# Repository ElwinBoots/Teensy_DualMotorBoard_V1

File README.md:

This project aims to deliver high performance (fast loops > 40 kHz, fast motion, and small following errors) brushless motor control.

## Videos in action 
See: https://www.youtube.com/@elwinboots2614

## Hardware 
- 1 Simple custom PCB for making connections
- 1 Teensy 4.1
- 2 DRV8301 motor drive boards, see Aliexpress
- 2 BLDC motors (sensorless or ABI encoders)
- 4 Pololu ACS711EX current sensor boards (drive boards have low side sensors. Prefer to use these instead to have in line sensing)

## Firmware
See firmware folder. Almost all code can be found in Firmware.ino. 

### Software to build firmware
"Old" Arduino IDE
- Arduino IDE 1.8.19 https://www.arduino.cc/en/software (Legacy IDE)
- Teensyduino https://www.pjrc.com/teensy/td_download.html (Follow the "Arduino 1.8.x Software Development" steps)
Or,
"New" Arduino IDE:
- Arduino IDE https://www.arduino.cc/en/software (current version: 2.2.1)
- Teensyduino https://www.pjrc.com/teensy/td_download.html (Follow the "Arduino 2.0.x Software Development" steps
 
If you want to test with 1 or 0 DRV8301 boards connected, search for the line: SPI_init( SSPIN ); and/or SPI_init( SSPIN2 ); and comment them out. With these lines commented the firmware and software can run without boards. With these lines the board waits for the DRV8301 boards, before continuing to boot.

Almost all parameters are defined in defines.h. All of these are accessible (read and write) from the host pc using the software provided. 

To add a variable and make it accessible from the PC:
1. Add parameter in defines.h 
2. run "gentracefile (Run this to update trace.h).bat". 
3. Compile and download Firmware.ino in Arduino IDE

Note: I use the 816 Mhz (overclock) option in the CPU speed menu.

## Software
- Python 3.x
- Spyder
- Code in Software folder

### To install: 
1. Download latest version of Python: https://www.python.org/downloads/
2. Install Python
3. In a command window, run `pip install spyder`
4. Run Spyder (C:\Users\XXX\AppData\Local\Programs\Python\PythonXXX\Scripts\spyder.exe)

### To use: 
1. In Spyder, run first cell (ctrl + enter) in test_object.py (for any missing modules, run `pip install <modulename>` in a cmd window.
2. When a Teensy is found with the correct firmware, you should get: "Connected to Teensy on COMX with serial number: XXXXXXXX."
3. Check that the LED on the Teensy is off. If it is still on, make check connection and power to DRV8301 boards, or comment out SPI_init( SSPIN ); and/or SPI_init( SSPIN2 ) to test without DRV8301 boards.
4. Now you can type `motor` in the IPython console, and it should show all parameters:\

5. To see for example only the configuration of motor 1, you can type `motor.conf1`:\

6. To retreive a single variable, just type the variable name and click enter. Example: `motor.state1.encoderPos1`. Note that you can use `tab` to autocomplete the name of a variable.
7. To set a variable, simply write a value to it. Example: `motor.conf1.commutationoffset = 0`, or use `m.setpar('motor.conf1.commutationoffset',0)`\
\
The setting of variables is fast. Almost 20000 values can be written in 1 second when writing one by one (even more when using arrays):\

### Tracing
To trace variables/signals: 
1. Use m.setTrace() to select signals. Example: `m.setTrace([ 'motor.state1.emech' , 'motor.state1.rmech' , 'motor.state1.ymech' ])`
2. Use `df = m.trace(2)` to trace for 2 seconds.
3. To plot, use `df.plot()`

Note1: By default tracing occurs at the full sample rate. Up to 50 signals at 60 kHz is possible. Downsampling is also possible to reduce load.\
Note2: All communication is in binary. This means that no precision is lost in the tracing.

### Tracing (background)
For non-blocking tracing of variables/signals:
1. Use m.setTrace() to select signals. Example: `m.setTrace([ 'motor.state1.emech' , 'motor.state1.rmech' , 'motor.state1.ymech' ])`
2. Use `m.tracebg( )` to start a background trace.
3. Use `df = m.stoptracegetdata()` to stop the trace and get the data
4. To plot, use `df.plot()`

Note: during the tracing you can still set variables. You can however not retrieve other variables.

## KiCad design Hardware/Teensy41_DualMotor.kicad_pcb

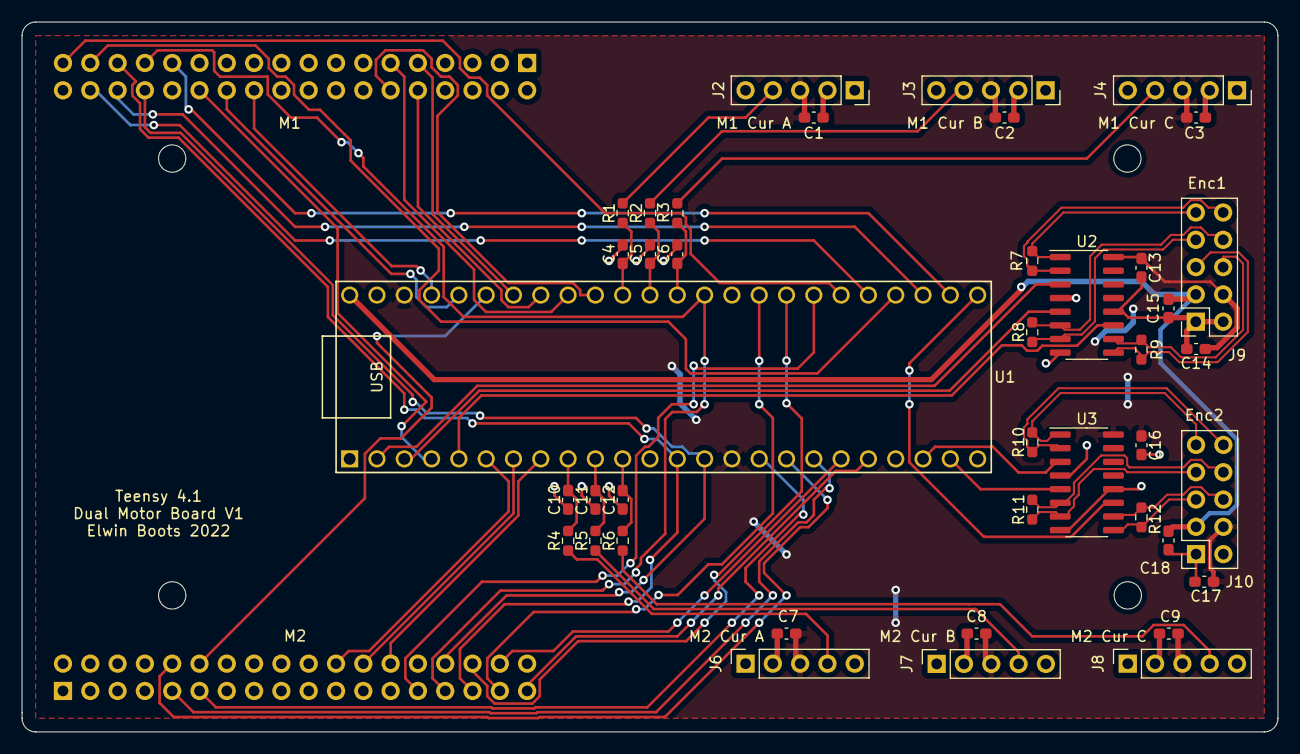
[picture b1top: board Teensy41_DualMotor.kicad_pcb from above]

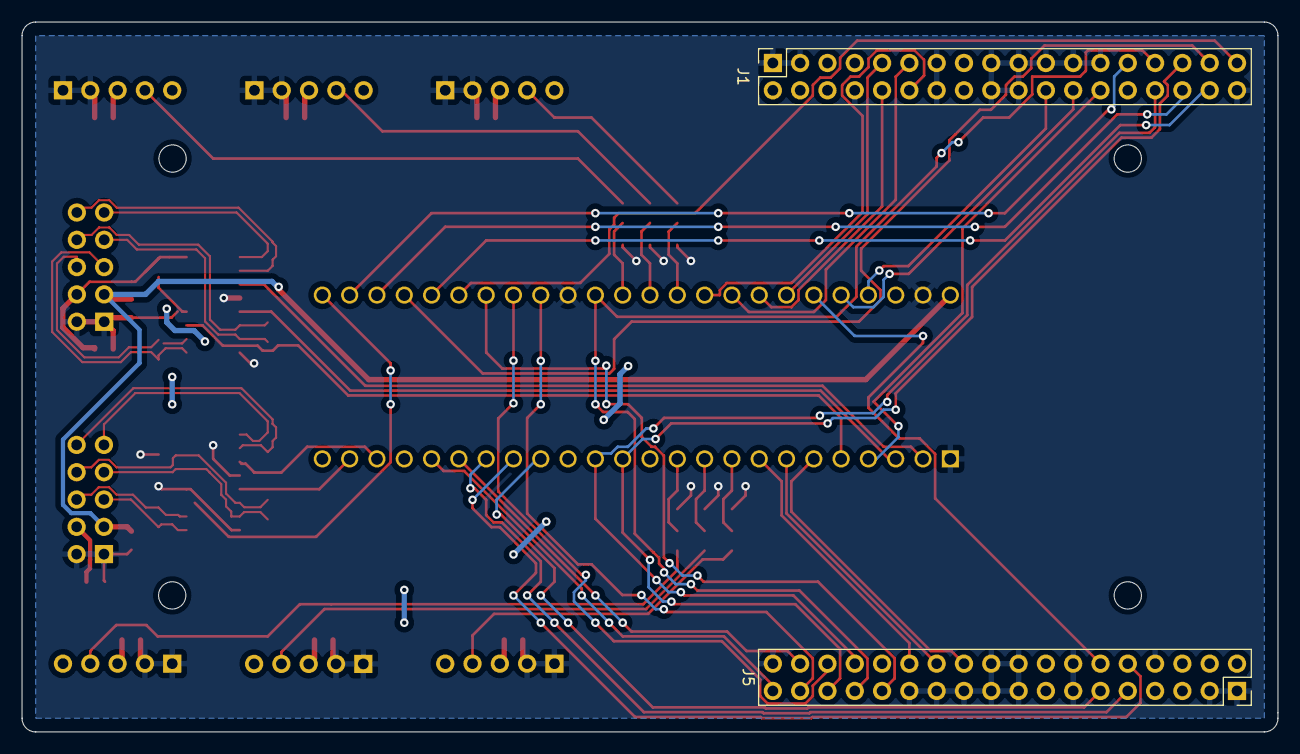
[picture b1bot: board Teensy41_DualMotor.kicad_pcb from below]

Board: 2 copper layers, 116.8 x 66.0 mm, 43 parts (2 on the bottom side), 60 nets.

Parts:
C1, C2, C3, C7, C8, C9, C13, C14, C15, C16, C17, C18: 0.1u; C_0603_1608Metric_Pad1.08x0.95mm_HandSolder
C4, C5, C6, C10, C11, C12: 15n; C_0603_1608Metric_Pad1.08x0.95mm_HandSolder
J1, J5: Conn_02x18_Odd_Even; PinSocket_2x18_P2.54mm_Vertical
J2, J3, J4, J6, J7, J8: Conn_01x05; PinSocket_1x05_P2.54mm_Vertical
J9, J10: Conn_02x05_Odd_Even; PinSocket_2x05_P2.54mm_Vertical
R1, R2, R3, R4, R5, R6: 1k; R_0603_1608Metric_Pad0.98x0.95mm_HandSolder
R7, R8, R9, R10, R11, R12: 120; R_0603_1608Metric_Pad0.98x0.95mm_HandSolder
U1: Teensy4.1; Teensy41
U2, U3: AM26LV32xD; SOIC-16_3.9x9.9mm_P1.27mm

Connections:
+3V3: C1.2, C2.2, C3.2, C7.2, C8.2, C9.2, C13.2, C14.2, C16.2, C17.2, J2.3, J3.3, J4.3, J6.3, J7.3, J8.3, J9.4, J10.4, U1.15 (3V3), U1.46 (3V3), U2.16 (VDD), U3.16 (VDD)
+5V: C15.2, C18.2, J9.3, J10.3, U1.48 (VIN)
EMF-A: J1.11, U1.40 (18_A4_SDA)
EMF-A2: J5.11, U1.16 (24_A10_TX6_SCL2)
EMF-B: J1.10, U1.41 (19_A5_SCL)
EMF-B2: J5.10, U1.17 (25_A11_RX6_SDA2)
EMF-C: J1.9, U1.42 (20_A6_TX5_LRCLK1)
EMF-C2: J5.9, U1.18 (26_A12_MOSI1)
EN-GATE: J1.27, U1.26 (34_RX8)
EN-GATE2: J5.27, U1.31 (39_MISO1_OUT1A)
ENC1_A: U1.2 (0_RX1_CRX2_CS1), U2.3 (1Y)
ENC1_A+: J9.10, R7.1, U2.2 (1A)
ENC1_A-: J9.9, R7.2, U2.1 (1B)
ENC1_B: U1.3 (1_TX1_CTX2_MISO1), U2.5 (2Y)
ENC1_B+: J9.8, R8.1, U2.6 (2A)
ENC1_B-: J9.7, R8.2, U2.7 (2B)
ENC1_I: U1.5 (3_LRCLK2), U2.11 (3Y)
ENC1_I+: J9.6, R9.1, U2.10 (3A)
ENC1_I-: J9.5, R9.2, U2.9 (3B)
ENC2_A: U1.22 (30_CRX3), U3.3 (1Y)
ENC2_A+: J10.10, R10.1, U3.2 (1A)
ENC2_A-: J10.9, R10.2, U3.1 (1B)
ENC2_B: U1.23 (31_CTX3), U3.5 (2Y)
ENC2_B+: J10.8, R11.1, U3.6 (2A)
ENC2_B-: J10.7, R11.2, U3.7 (2B)
ENC2_I: U1.25 (33_MCLK2), U3.11 (3Y)
ENC2_I+: J10.6, R12.1, U3.10 (3A)
ENC2_I-: J10.5, R12.2, U3.9 (3B)
GND: C1.1, C2.1, C3.1, C4.2, C5.2, C6.2, C7.1, C8.1, C9.1, C10.2, C11.2, C12.2, C13.1, C14.1, C15.1, C16.1, C17.1, C18.1, J1.1, J1.3, J1.8, J1.13, J1.14, J1.17, J1.18, J1.19, J1.20, J1.21, J1.23, J1.25, J1.36, J2.1, J2.2, J3.1, J3.2, J4.1, J4.2, J5.1, J5.3, J5.8, J5.13, J5.14, J5.17, J5.18, J5.19, J5.20, J5.21, J5.23, J5.25, J5.36, J6.1, J6.2, J7.1, J7.2, J8.1, J8.2, J9.1, J9.2, J10.1, J10.2, U1.1 (GND), U1.34 (GND), U1.47 (GND), U2.4 (G), U2.8 (GND), U2.12 (~G), U3.4 (G), U3.8 (GND), U3.12 (~G)
INH-A: J1.26, U1.4 (2_OUT2)
INH-A2: J5.26, U1.8 (6_OUT1D)
INH-B: J1.24, U1.44 (22_A8_CTX1)
INH-B2: J5.24, U1.7 (5_IN2)
INH-C: J1.22, U1.45 (23_A9_CRX1_MCLK1)
INH-C2: J5.22, U1.6 (4_BCLK2)
I_PH_A: J2.4, R1.1
I_PH_A2: J6.4, R4.1
I_PH_A2_Filt: C10.1, R4.2, U1.9 (7_RX2_OUT1A)
I_PH_A_Filt: C4.1, R1.2, U1.38 (16_A2_RX4_SCL1)
I_PH_B: J3.4, R2.1
I_PH_B2: J7.4, R5.1
I_PH_B2_Filt: C11.1, R5.2, U1.10 (8_TX2_IN1)
I_PH_B_Filt: C5.1, R2.2, U1.37 (15_A1_RX3_SPDIF_IN)
I_PH_C: J4.4, R3.1
I_PH_C2: J8.4, R6.1
I_PH_C2_Filt: C12.1, R6.2, U1.11 (9_OUT1C)
I_PH_C_Filt: C6.1, R3.2, U1.36 (14_A0_TX3_SPDIF_OUT)
PWRGD: J1.35, U1.30 (38_CS1_IN1)
PWRGD2: J5.35, U1.20 (28_RX7)
SCLK: J1.29, J5.29, U1.35 (13_SCK_LED)
SDI: J1.31, J5.31, U1.13 (11_MOSI_CTX1)
SDO: J1.30, J5.30, U1.14 (12_MISO_MQSL)
VPDD-O: J1.12, U1.39 (17_A3_TX4_SDA1)
VPDD-O2: J5.12, U1.43 (21_A7_RX5_BCLK1)
nFAULT: J1.33, U1.28 (36_CS)
nFAULT2: J5.33, U1.33 (41_A17)
nOCTW: J1.34, U1.29 (37_CS)
nOCTW2: J5.34, U1.19 (27_A13_SCK1)
nSCS: J1.32, U1.27 (35_TX8)
nSCS2: J5.32, U1.32 (40_A16)

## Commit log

2022-03-18 Teensy Dual Motor Control
    First version on GIT
2022-03-18 Inlude the Python script
2022-03-18 New current controller: PI with Tustin integrator
2022-03-18 Bugfix Ts should not be an integer, otherwise wrong controller gains when running 60 kHz.
2022-04-15 Before large cleanup
2022-04-15 fix typo
2022-04-15 Add Python side
2022-04-15 Add Matlab
2022-04-15 Cleanup and fixed warnings
2022-04-15 Small cleanup, added dependencies
2022-04-17 Increased traceable signals to 30
    Increasing to 62 was too much, prbs current plant showed it was not always in time (noisy phase near nyquist frequency)
2022-04-17 Decrease timout: Faster serial readall
2022-04-17 Increased timeout. Tracing was not stable.
2022-04-22 ParameterTree test
2022-04-22 Sendall now compatible with n_trace variable.
2022-04-23 Added lowpass for VBus and HFI. Minor cleanup. HFI now uses trapezoidal integrator.
2022-05-04 Add HFI feedforward and corrected gain
2022-05-04 Add power and bus current calculations. Minor cleanup.
2022-05-19 Add PCB design
2022-05-19 Add PDF of PCB schematic
2022-09-07 Add missing make3 file
2022-12-27 Large update to use variables in structures. Preparation for simpler dual motor control.
2022-12-27 Changed motor 2 current inputs
    Chosen inputs turned out to not work for analog input.
2023-01-04 Remove old debug line
2023-05-15 Change macros names to capital letters
2023-05-28 Changed leadlag to series PID with first order lowpass. Changed Tustin integrators to normal integrators.
2023-05-29 Cleanup
2023-05-29 Add nyquist plot
2023-05-29 2 Motors now working
2023-06-04 Added Biquad filters to control loops for lowpass and notches
2023-06-04 Fixed initialization of Biquad filters
2023-06-04 Fixed issue where wrong variable was passed to velocity feedforward
2023-06-10 Use doubles for setpoint to improve accuracy
2023-06-10 Add biquad filters for current controllers
2023-06-10 Encoders minor update
2023-06-10 Split feedforward signals for tracing
2023-06-10 More setpoint features Offset velocity improved Controller tuning in Python
2023-06-11 Python: Added pos_wait() command which does a move and then waits for it to finish
2023-06-11 Remove file
2023-06-12 Fix current loop integrators Implement getsigid
2023-06-12 Fixed bug that caused traces of 1e6 samples or more not to work
2023-06-17 Minor changes
2023-06-18 Cleanup Fix small glitch on turning on Corrected voltage feedforward Added streaming functionality to stream setpoint from pc Readall now has option to ignore large arrays
2023-07-09 Added filtering in parametertree Cleanup
2023-10-09 Object oriented interfacing via motorclass.py Added autocompletion to all variables Added motor object that allows for easy access to all variables (set and get) Tracing of 50 signals @60 kHz
2023-12-27 Added threading and background trace
2023-12-30 Cleanup: Put files in folders and some renaming Make more use of objects Added check before sending data over serial: prevent strange motor behaviour
2024-01-06 Added timeout in the connecting to Teensy Changed hfi_abs_pos to double Adjusted rel setpoint option to wait without getsig (such that tracebg can be running)
2024-01-06 Added receivedVal16 initialization
2024-01-06 Cleanup: Use function for angle normalization
2024-01-20 Changed HFI so that it should also work on low side shunts Removed stateX->thetaPark speed limit Added option for mp3 playback
2024-02-04 Transfer errors no longer cause error, but still avoid crashing Teensy when PC is not reading buffer
2024-02-04 Improved HFI: Corrected scaling. Added error clipping. HFI lowpass now works. Added 45 degrees HFI. Added comments.
2024-02-06 Add current offset ramp. Add truncate to stateX->hfi_dir_int to avoid runaway integrator (not too small to not impact startup). Encoder commutation calculation inside 2*pi
2024-02-13 Minor efficiency changes
2024-12-24 Fix encoder issue that caused issues when enccountperrev/N_pp was not an integer.
2024-12-24 Added posibility to enable/disable the usage of V7 (enabled = measure current and run loop twice per PWM cycle (V0 and V7), diabled = once per PWM cycle (V0))
